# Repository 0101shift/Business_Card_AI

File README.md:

# Business_Card_AI

Business card design on a PCB, isn't it crazy!!? An eye catching design fusing electronics with a bit astronomy comes out really well. And the card is also integrated with NFC tag which links to my portfolio whenever tapped. With the energy harvesting feature, NFC IC generates enough power to light up the LED circuit on the card.

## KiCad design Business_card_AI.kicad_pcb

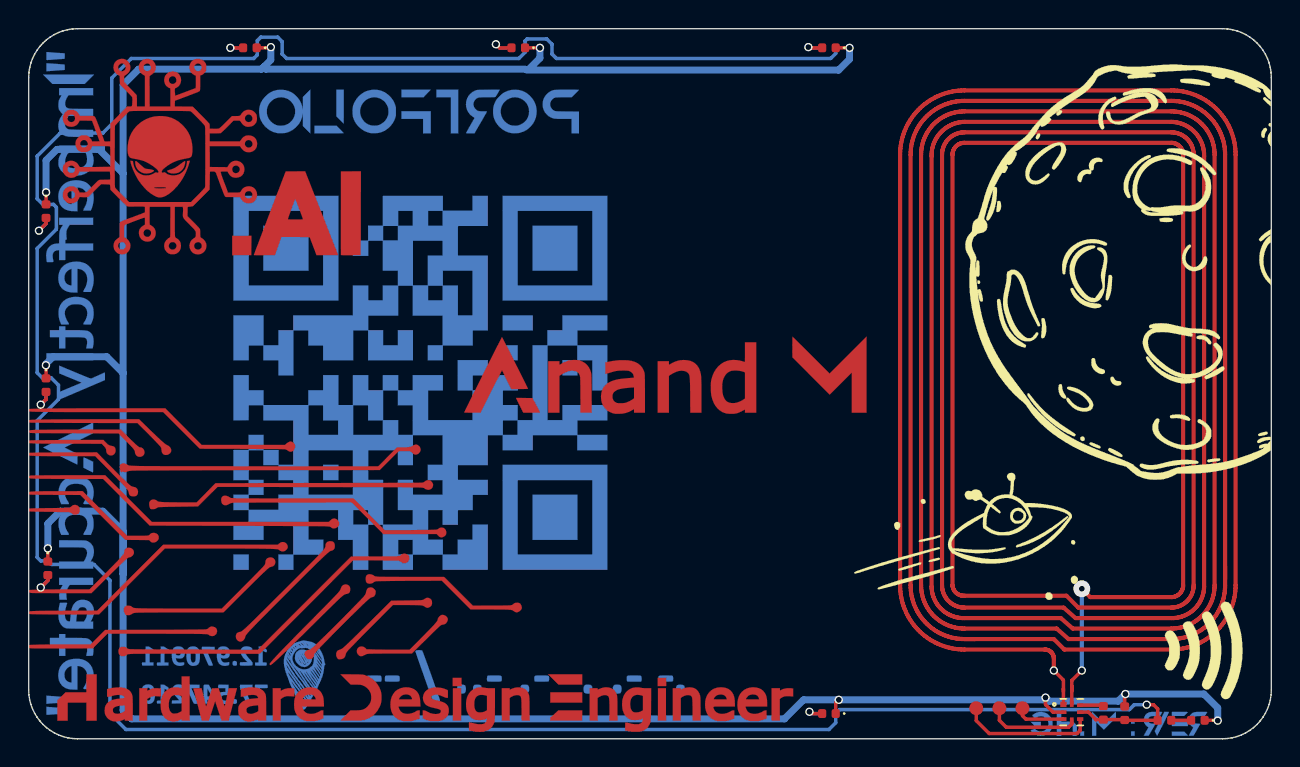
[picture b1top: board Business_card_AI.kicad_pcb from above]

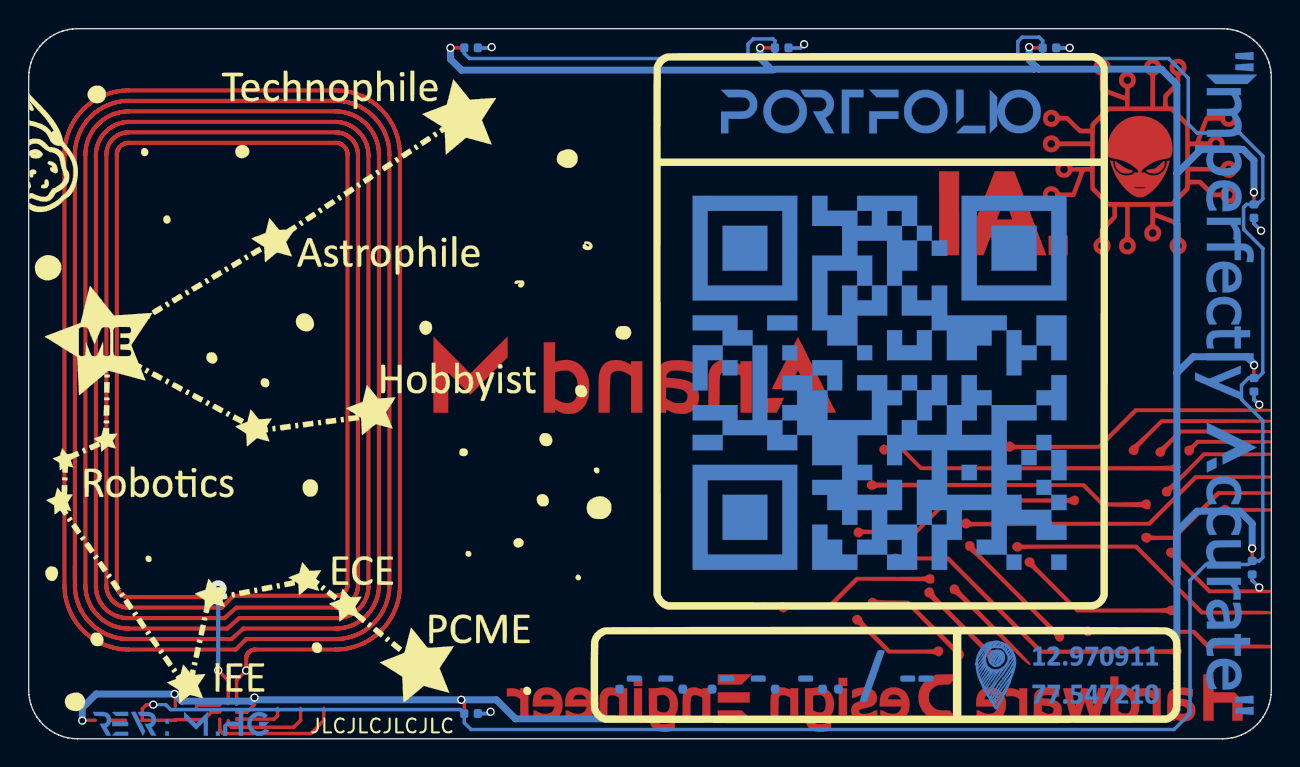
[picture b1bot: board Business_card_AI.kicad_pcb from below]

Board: 2 copper layers, 88.9 x 50.8 mm, 22 parts (7 on the bottom side), 15 nets.

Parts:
C1: 220nF; C_0402_1005Metric
D1, D2, D3, D4, D5, D6, D7, D8: LED; LED_0402_1005Metric
R1: 0E; R_0402_1005Metric
R2, R3, R4, R5, R6, R7, R8, R9: 270E; R_0402_1005Metric
TP1, TP2, TP3: TestPoint; TestPoint_Pad_D1.0mm
U1: NT3H1101W0FHKH

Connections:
+BATT: C1.1, R1.2, R2.1, R3.1, R4.1, R5.1, R6.1, R7.1, R8.1, R9.1, U1.6
GND: C1.2, D1.1, D2.1, D3.1, D4.1, D5.1, D6.1, D7.1, D8.1, U1.2
unnamed: D1.2, R2.2
unnamed: D2.2, R3.2
unnamed: D3.2, R4.2
unnamed: D4.2, R5.2
unnamed: D5.2, R6.2
unnamed: D6.2, R7.2
unnamed: D7.2, R8.2
unnamed: D8.2, R9.2
unnamed: R1.1, U1.7
unnamed: TP1.1, U1.3
unnamed: TP2.1, U1.5
unnamed: TP3.1, U1.4
unnamed: U1.1, U1.8

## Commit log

2022-11-06 Update README.md
    Updated readme
2022-11-06 Update README.md
    Added Images
2022-11-06 Add files via upload
    Added design files
